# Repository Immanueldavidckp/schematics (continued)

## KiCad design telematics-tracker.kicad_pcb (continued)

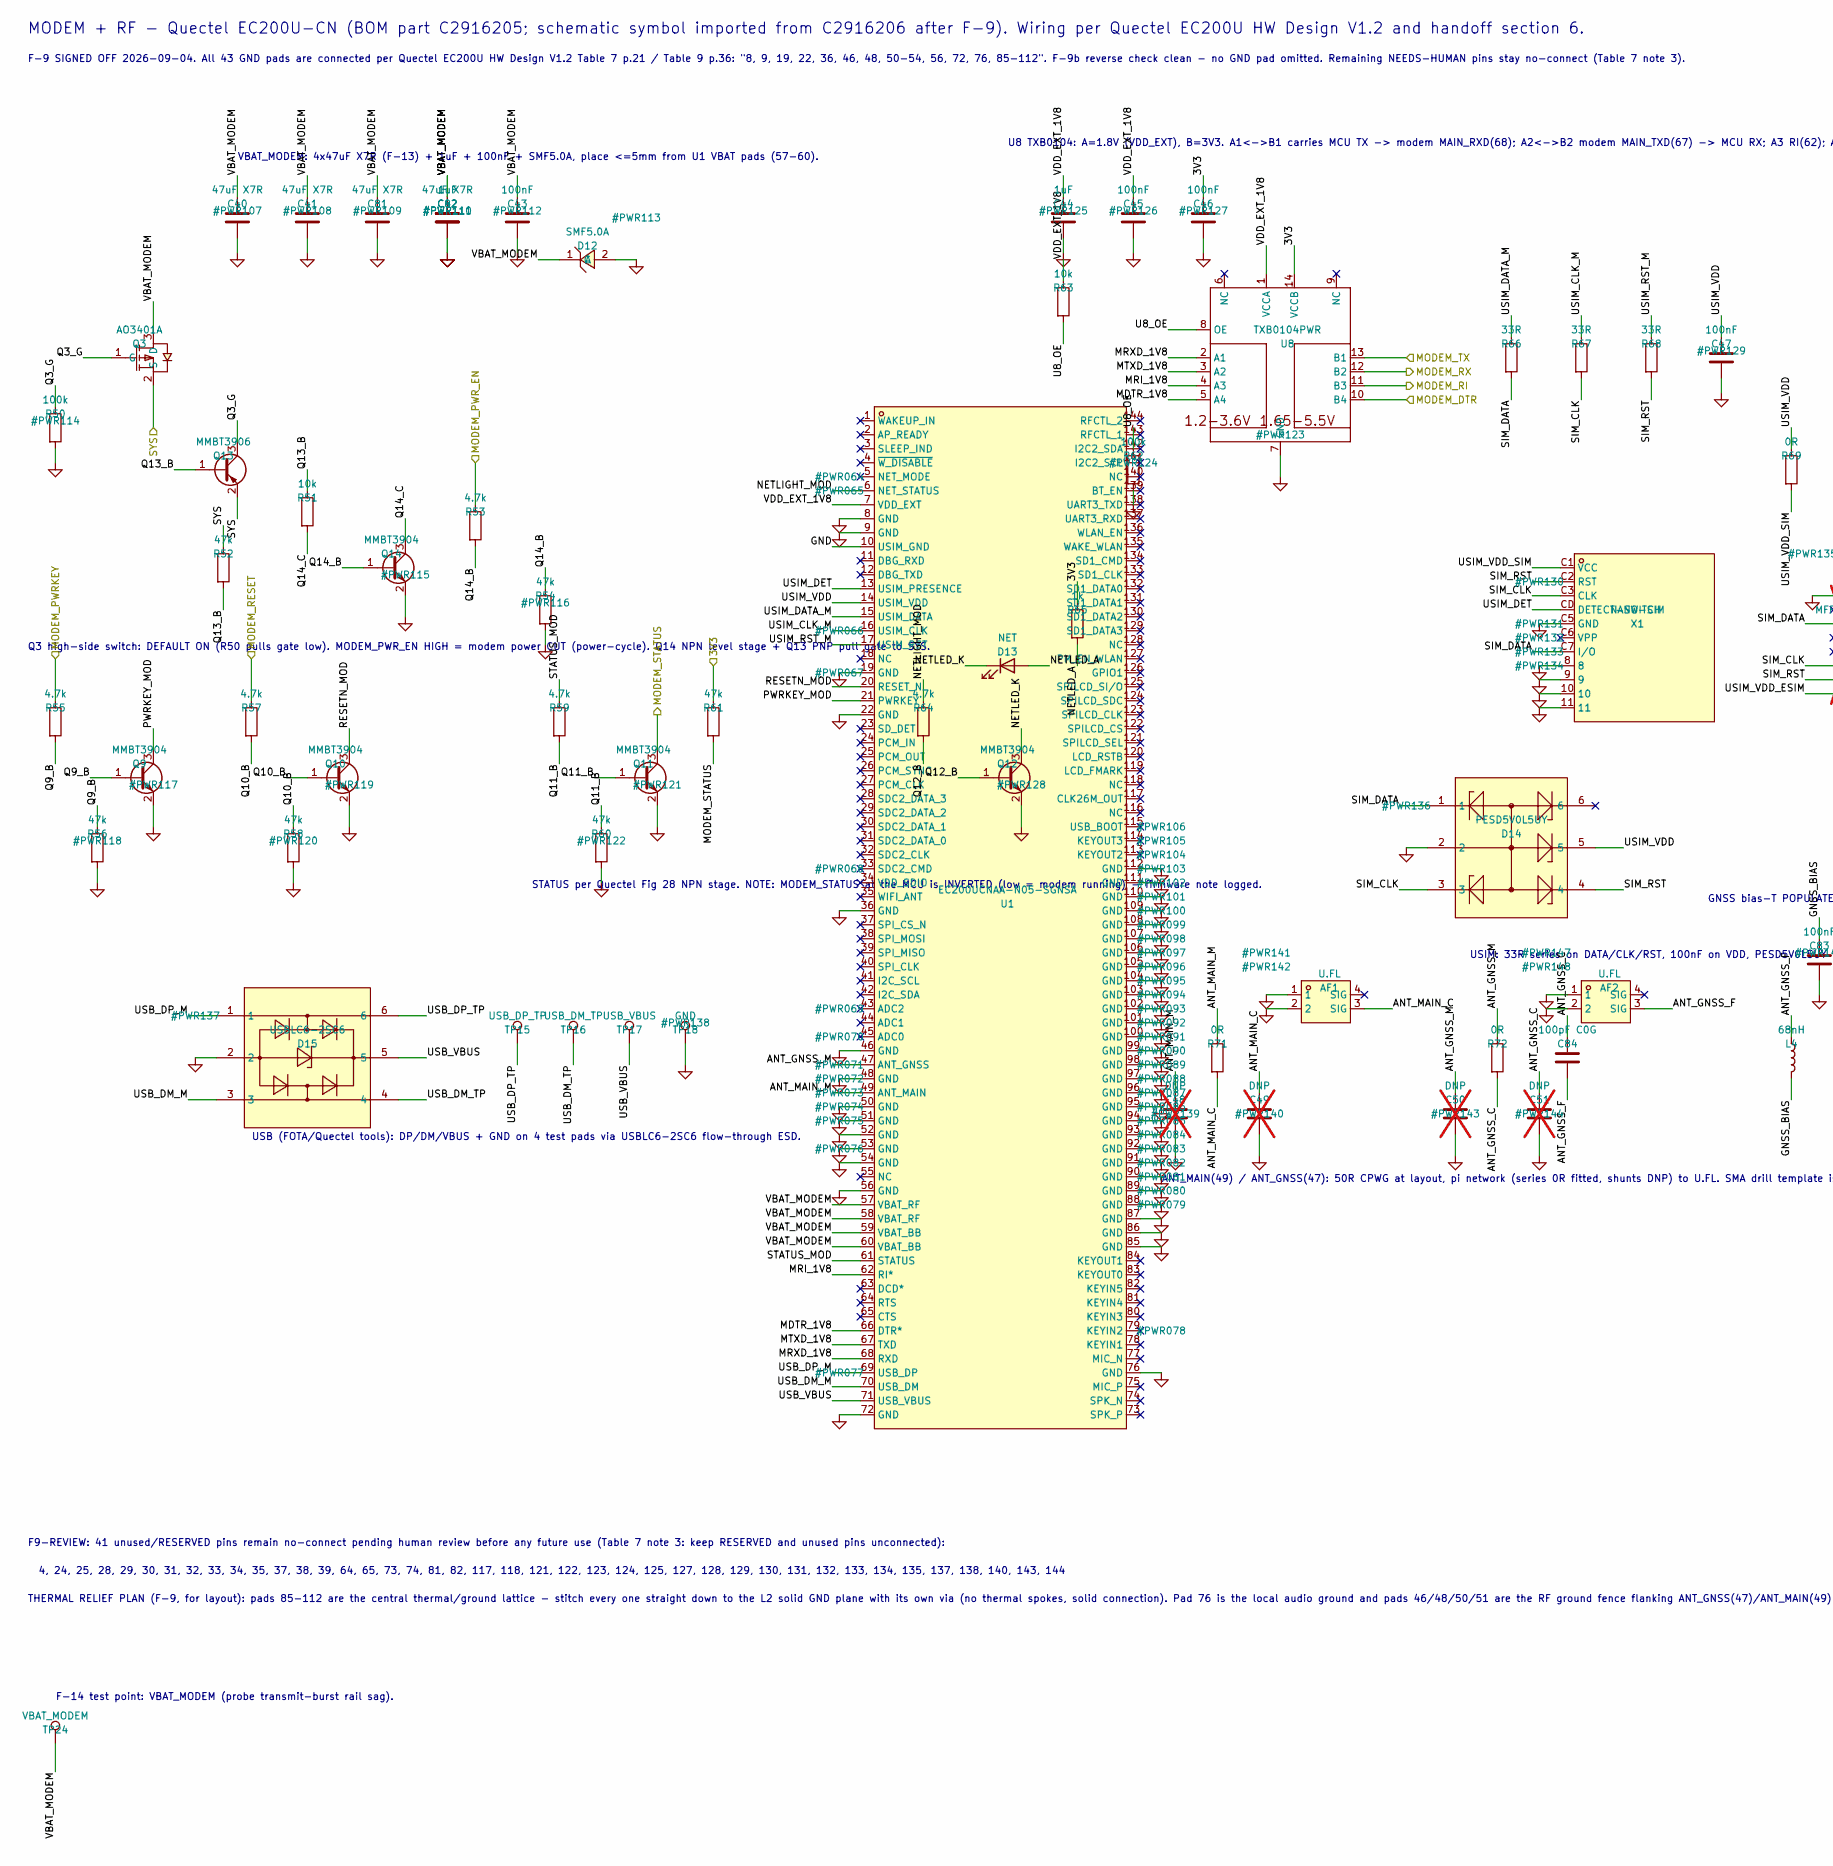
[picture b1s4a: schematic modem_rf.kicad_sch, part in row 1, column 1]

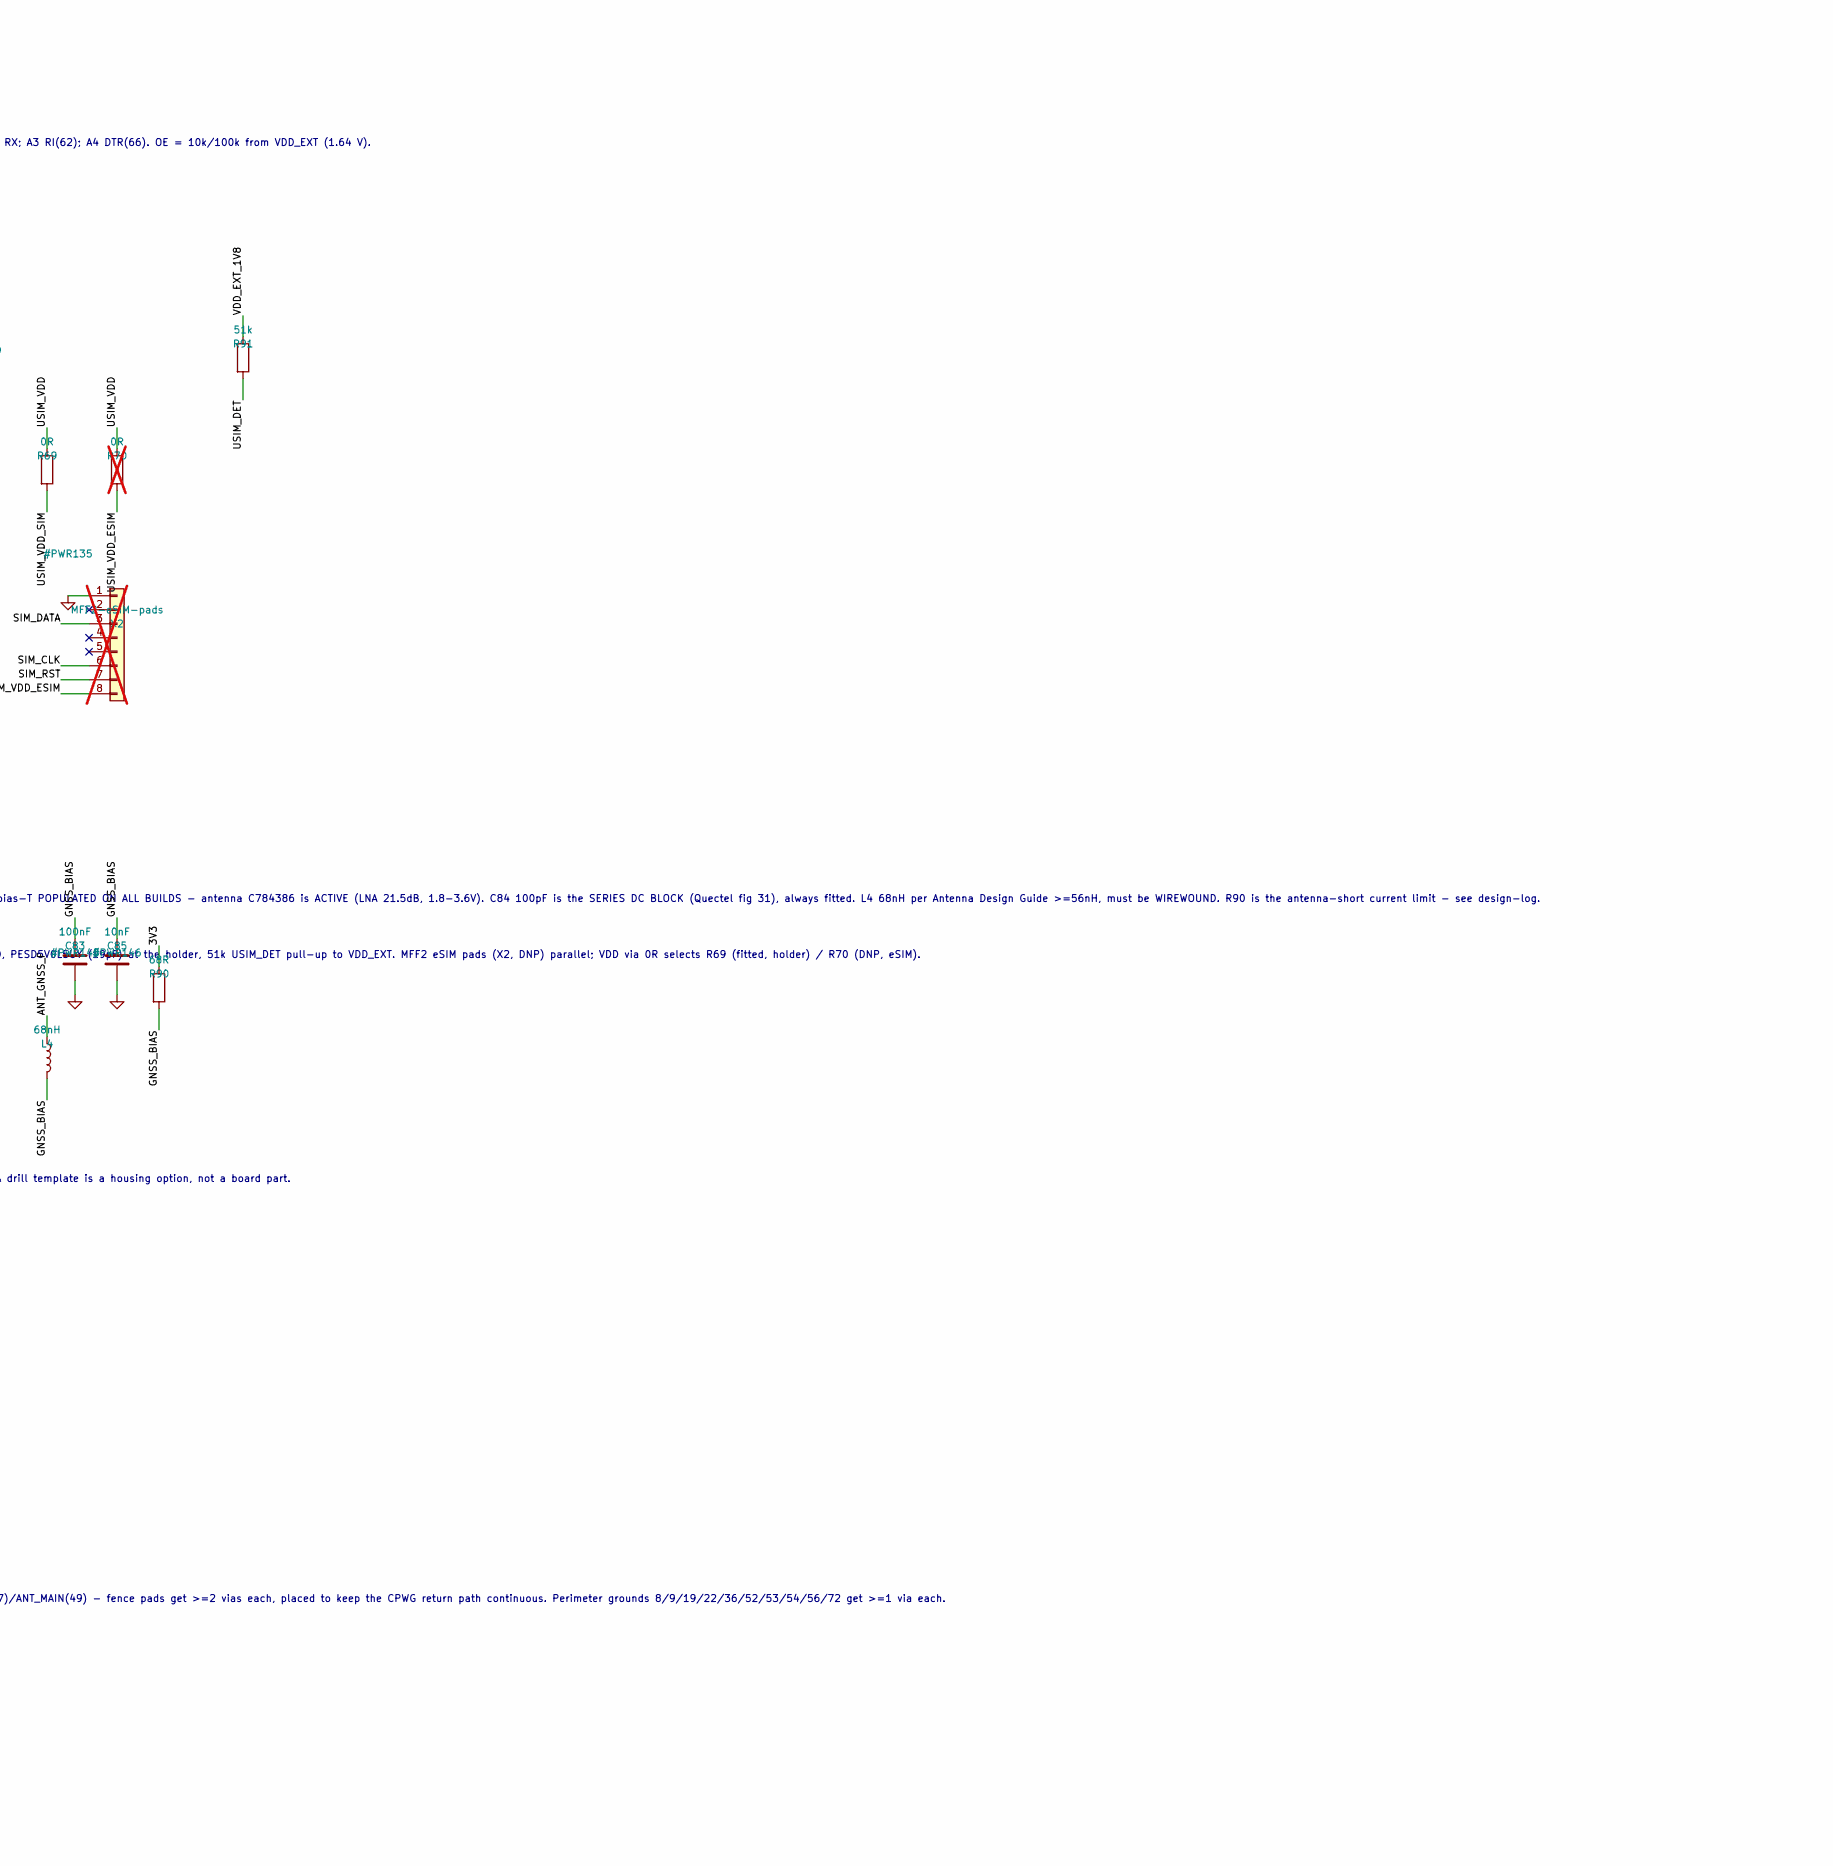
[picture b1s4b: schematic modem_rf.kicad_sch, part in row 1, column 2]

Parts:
AF1, AF2: U.FL; CONN-SMD_XY-IPEX1; LCSC C53133524
C40, C41, C81, C82: 47uF X7R; C_1210_3225Metric; LCSC C84494
C42, C44: 1uF; C_0603_1608Metric; LCSC C106858
C43, C45, C46, C47: 100nF; C_0603_1608Metric; LCSC C14663
C48, C49, C50, C51: DNP; C_0402_1005Metric; not fitted
C83: 100nF; C_0402_1005Metric; LCSC C1525
C84: 100pF C0G; C_0402_1005Metric; LCSC C1546
C85: 10nF; C_0402_1005Metric; LCSC C15195
D12: SMF5.0A; SOD-123FL_L2.7-W1.8-LS3.8-RD; LCSC C193402
D13: NET; LED_0603_1608Metric; LCSC C2286
D14: PESD5V0L5UY; SOT-363_L2.0-W1.3-P0.65-LS2.1-BR; LCSC C179747
D15: USBLC6-2SC6; SOT-23-6_L2.9-W1.6-P0.95-LS2.8-BL; LCSC C7519
L4: 68nH; L_0402_1005Metric; LCSC C3221844
Q3: AO3401A; SOT-23-3_L2.9-W1.3-P1.90-LS2.4-BR; LCSC C15127
Q9, Q10, Q11, Q12, Q14: MMBT3904; SOT-23; LCSC C20526
Q13: MMBT3906; SOT-23; LCSC C75549
R50, R62: 100k; R_0805_2012Metric; LCSC C149504
R51, R63: 10k; R_0805_2012Metric; LCSC C17414
R52, R54, R56, R58, R60, R61: 47k; R_0805_2012Metric; LCSC C17713
R53, R55, R57, R59, R64: 4.7k; R_0805_2012Metric; LCSC C17673
R65: 1k; R_0805_2012Metric; LCSC C17513
R66, R67, R68: 33R; R_0805_2012Metric; LCSC C17634
R69: 0R; R_0805_2012Metric; LCSC C17477
R70: 0R; R_0805_2012Metric; LCSC C17477; not fitted
R71, R72: 0R; R_0402_1005Metric; LCSC C17168
R90: 68R; R_1210_3225Metric; LCSC C137091
R91: 51k; R_0603_1608Metric; LCSC C23196
TP15: USB_DP_TP; TestPoint_Pad_D1.5mm
TP16: USB_DM_TP; TestPoint_Pad_D1.5mm
TP17: USB_VBUS; TestPoint_Pad_D1.5mm
TP18: GND; TestPoint_Pad_D1.5mm
TP24: VBAT_MODEM; TestPoint_Pad_D1.5mm
U1: EC200UCNAA-N05-SGNSA; LCC-LGA-144_L31.0-W28.0-P1.30_L610-CN-02; LCSC C2916205
U8: TXB0104PWR; TSSOP-14_L5.0-W4.4-P0.65-LS6.4-BL; LCSC C60708
X1: NANO-SIM; SIM-SMD_YKSIM-PUSH137-140NANO; LCSC C53207808
X2: MFF2-eSIM-pads; eSIM_MFF2_VFDFPN8; LCSC DNP-MFF2; not fitted

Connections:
3V3: C46.1, R61.1, R65.1, R90.1, U8.14 (VCCB); also elsewhere on the board
/modem_rf/ANT_GNSS_C: C51.1, C84.1, R72.2
/modem_rf/ANT_GNSS_F: AF2.3 (SIG), C84.2, L4.1
/modem_rf/ANT_GNSS_M: C50.1, R72.1, U1.47 (ANT_GNSS)
/modem_rf/ANT_MAIN_C: AF1.3 (SIG), C49.1, R71.2
/modem_rf/ANT_MAIN_M: C48.1, R71.1, U1.49 (ANT_MAIN)
/modem_rf/GNSS_BIAS: C83.1, C85.1, L4.2, R90.2
/modem_rf/MDTR_1V8: U1.66 (DTR*), U8.5 (A4)
/modem_rf/MRI_1V8: U1.62 (RI*), U8.4 (A3)
/modem_rf/MRXD_1V8: U1.68 (RXD), U8.2 (A1)
/modem_rf/MTXD_1V8: U1.67 (TXD), U8.3 (A2)
/modem_rf/NETLED_A: D13.2 (A), R65.2
/modem_rf/NETLED_K: D13.1 (K), Q12.3 (C)
/modem_rf/NETLIGHT_MOD: R64.1, U1.6 (NET_STATUS)
/modem_rf/PWRKEY_MOD: Q9.3 (C), U1.21 (PWRKEY)
/modem_rf/Q3_G: Q3.1 (G), Q13.3 (C), R50.1
/modem_rf/Q9_B: Q9.1 (B), R55.2, R56.1
/modem_rf/Q10_B: Q10.1 (B), R57.2, R58.1
/modem_rf/Q11_B: Q11.1 (B), R59.2, R60.1
/modem_rf/Q12_B: Q12.1 (B), R64.2
/modem_rf/Q13_B: Q13.1 (B), R51.1, R52.2
/modem_rf/Q14_B: Q14.1 (B), R53.2, R54.1
/modem_rf/Q14_C: Q14.3 (C), R51.2
/modem_rf/RESETN_MOD: Q10.3 (C), U1.20 (RESET_N)
/modem_rf/SIM_CLK: D14.3, R67.2, X1.C3 (CLK), X2.6
/modem_rf/SIM_DATA: D14.1, R66.2, X1.C7 (I/O), X2.3
/modem_rf/SIM_RST: D14.4, R68.2, X1.C2 (RST), X2.7
/modem_rf/STATUS_MOD: R59.1, U1.61 (STATUS)
/modem_rf/U8_OE: R62.1, R63.2, U8.8 (OE)
/modem_rf/USB_DM_M: D15.3, U1.70 (USB_DM)
/modem_rf/USB_DM_TP: D15.4, TP16.1
/modem_rf/USB_DP_M: D15.1, U1.69 (USB_DP)
/modem_rf/USB_DP_TP: D15.6, TP15.1
/modem_rf/USB_VBUS: D15.5, TP17.1, U1.71 (USB_VBUS)
/modem_rf/USIM_CLK_M: R67.1, U1.16 (USIM_CLK)
/modem_rf/USIM_DATA_M: R66.1, U1.15 (USIM_DATA)
/modem_rf/USIM_DET: R91.2, U1.13 (USIM_PRESENCE), X1.CD (DETECT-SWITCH)
/modem_rf/USIM_RST_M: R68.1, U1.17 (USIM_RST)
/modem_rf/USIM_VDD: C47.1, D14.5, R69.1, R70.1, U1.14 (USIM_VDD)
/modem_rf/USIM_VDD_ESIM: R70.2, X2.8
/modem_rf/USIM_VDD_SIM: R69.2, X1.C1 (VCC)
/modem_rf/VBAT_MODEM: C40.1, C41.1, C42.1, C43.1, C81.1, C82.1, D12.1 (C), Q3.3 (D), TP24.1, U1.57 (VBAT_RF), U1.58 (VBAT_RF), U1.59 (VBAT_BB), U1.60 (VBAT_BB)
/modem_rf/VDD_EXT_1V8: C44.1, C45.1, R63.1, R91.1, U1.7 (VDD_EXT), U8.1 (VCCA)
GND: AF1.1, AF1.2, AF2.1, AF2.2, C40.2, C41.2, C42.2, C43.2, C44.2, C45.2, C46.2, C47.2, C48.2, C49.2, C50.2, C51.2, C81.2, C82.2, C83.2, C85.2, D12.2 (A), D14.2, D15.2, Q9.2 (E), Q10.2 (E), Q11.2 (E), Q12.2 (E), Q14.2 (E), R50.2, R54.2, R56.2, R58.2, R60.2, R62.2, TP18.1, U1.8 (GND), U1.9 (GND), U1.10 (USIM_GND), U1.19 (GND), U1.22 (GND), U1.36 (GND), U1.46 (GND), U1.48 (GND), U1.50 (GND), U1.51 (GND), U1.52 (GND), U1.53 (GND), U1.54 (GND), U1.56 (GND), U1.72 (GND), U1.76 (GND), U1.85 (GND), U1.86 (GND), U1.87 (GND), U1.88 (GND), U1.89 (GND), U1.90 (GND), U1.91 (GND), U1.92 (GND), U1.93 (GND), U1.94 (GND), U1.95 (GND), U1.96 (GND), U1.97 (GND), U1.98 (GND), U1.99 (GND), U1.100 (GND), U1.101 (GND), U1.102 (GND), U1.103 (GND), U1.104 (GND), U1.105 (GND), U1.106 (GND), U1.107 (GND), U1.108 (GND), U1.109 (GND), U1.110 (GND), U1.111 (GND), U1.112 (GND), U8.7 (GND), X1.8, X1.9, X1.10, X1.11, X1.C5 (GND), X2.1; also elsewhere on the board
MODEM_DTR: U8.10 (B4); also elsewhere on the board
MODEM_PWRKEY: R55.1; also elsewhere on the board
MODEM_PWR_EN: R53.1; also elsewhere on the board
MODEM_RESET: R57.1; also elsewhere on the board
MODEM_RI: U8.11 (B3); also elsewhere on the board
MODEM_RX: U8.12 (B2); also elsewhere on the board
MODEM_STATUS: Q11.3 (C), R61.2; also elsewhere on the board
MODEM_TX: U8.13 (B1); also elsewhere on the board
SYS: Q3.2 (S), Q13.2 (E), R52.1; also elsewhere on the board

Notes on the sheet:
MODEM + RF - Quectel EC200U-CN (BOM part C2916205; schematic symbol imported from C2916206 after F-9). Wiring per Quectel EC200U HW Design V1.2 and handoff section 6.
F-9 SIGNED OFF 2026-09-04. All 43 GND pads are connected per Quectel EC200U HW Design V1.2 Table 7 p.21 / Table 9 p.36: "8, 9, 19, 22, 36, 46, 48, 50-54, 56, 72, 76, 85-112". F-9b reverse check clean - no GND pad omitted. Remaining NEEDS-HUMAN pins stay no-connect (Table 7 note 3).
F9-REVIEW: 41 unused/RESERVED pins remain no-connect pending human review before any future use (Table 7 note 3: keep RESERVED and unused pins unconnected):
4, 24, 25, 28, 29, 30, 31, 32, 33, 34, 35, 37, 38, 39, 64, 65, 73, 74, 81, 82, 117, 118, 121, 122, 123, 124, 125, 127, 128, 129, 130, 131, 132, 133, 134, 135, 137, 138, 140, 143, 144
THERMAL RELIEF PLAN (F-9, for layout): pads 85-112 are the central thermal/ground lattice - stitch every one straight down to the L2 solid GND plane with its own via (no thermal spokes, solid connection). Pad 76 is the local audio ground and pads 46/48/50/51 are the RF ground fence flanking ANT_GNS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
VBAT_MODEM: 4x47uF X7R (F-13) + 1uF + 100nF + SMF5.0A, place <=5mm from U1 VBAT pads (57-60).
F-14 test point: VBAT_MODEM (probe transmit-burst rail sag).
Q3 high-side switch: DEFAULT ON (R50 pulls gate low). MODEM_PWR_EN HIGH = modem power CUT (power-cycle). Q14 NPN level stage + Q13 PNP pull gate to SYS.
STATUS per Quectel Fig 28 NPN stage. NOTE: MODEM_STATUS at the MCU is INVERTED (low = modem running) - firmware note logged.
U8 TXB0104: A=1.8V (VDD_EXT), B=3V3. A1<->B1 carries MCU TX -> modem MAIN_RXD(68); A2<->B2 modem MAIN_TXD(67) -> MCU RX; A3 RI(62); A4 DTR(66). OE = 10k/100k from VDD_EXT (1.64 V).
USIM: 33R series on DATA/CLK/RST, 100nF on VDD, PESD5V0L5UY (19pF) at the holder, 51k USIM_DET pull-up to VDD_EXT. MFF2 eSIM pads (X2, DNP) parallel; VDD via 0R selects R69 (fitted, holder) / R70 (DNP, eSIM).
USB (FOTA/Quectel tools): DP/DM/VBUS + GND on 4 test pads via USBLC6-2SC6 flow-through ESD.
GNSS bias-T POPULATED ON ALL BUILDS - antenna C784386 is ACTIVE (LNA 21.5dB, 1.8-3.6V). C84 100pF is the SERIES DC BLOCK (Quectel fig 31), always fitted. L4 68nH per Antenna Design Guide >=56nH, must be WIREWOUND. R90 is the antenna-short current limit - see design-log.
ANT_MAIN(49) / ANT_GNSS(47): 50R CPWG at layout, pi network (series 0R fitted, shunts DNP) to U.FL. SMA drill template is a housing option, not a board part.

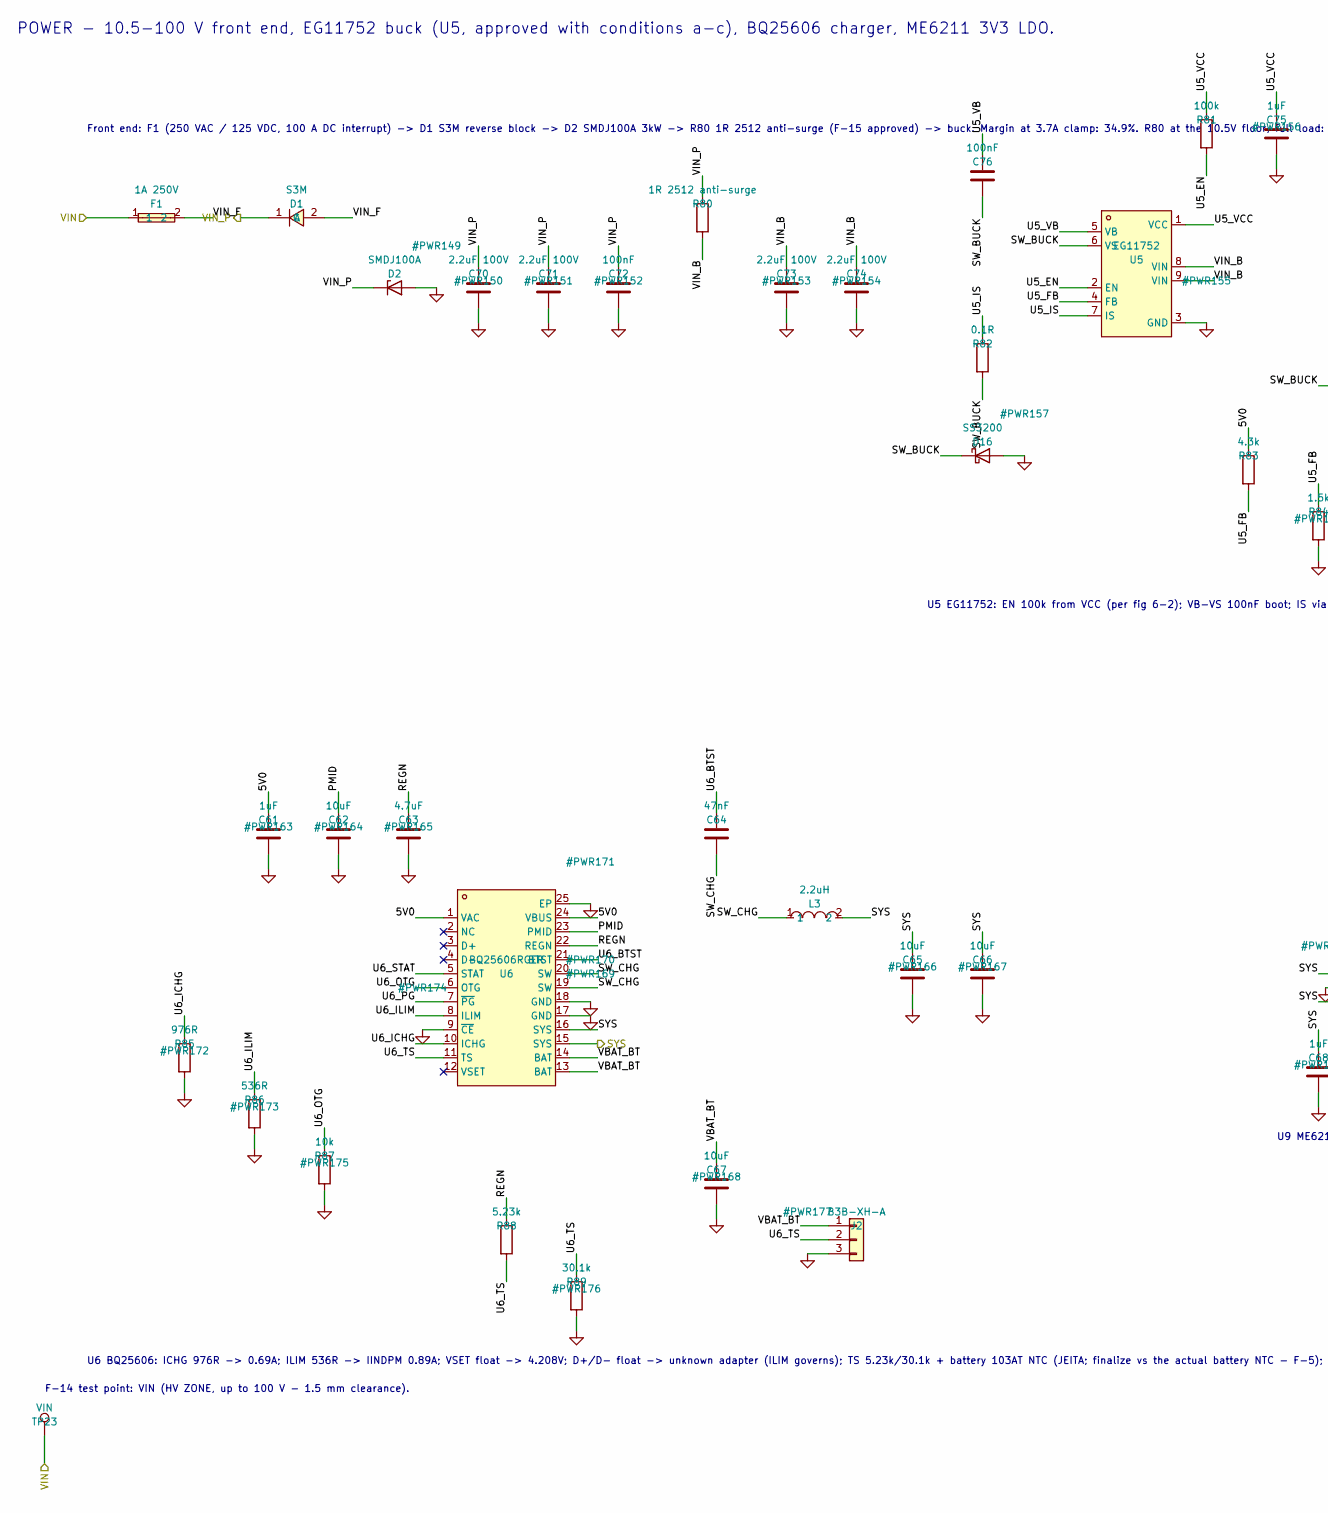
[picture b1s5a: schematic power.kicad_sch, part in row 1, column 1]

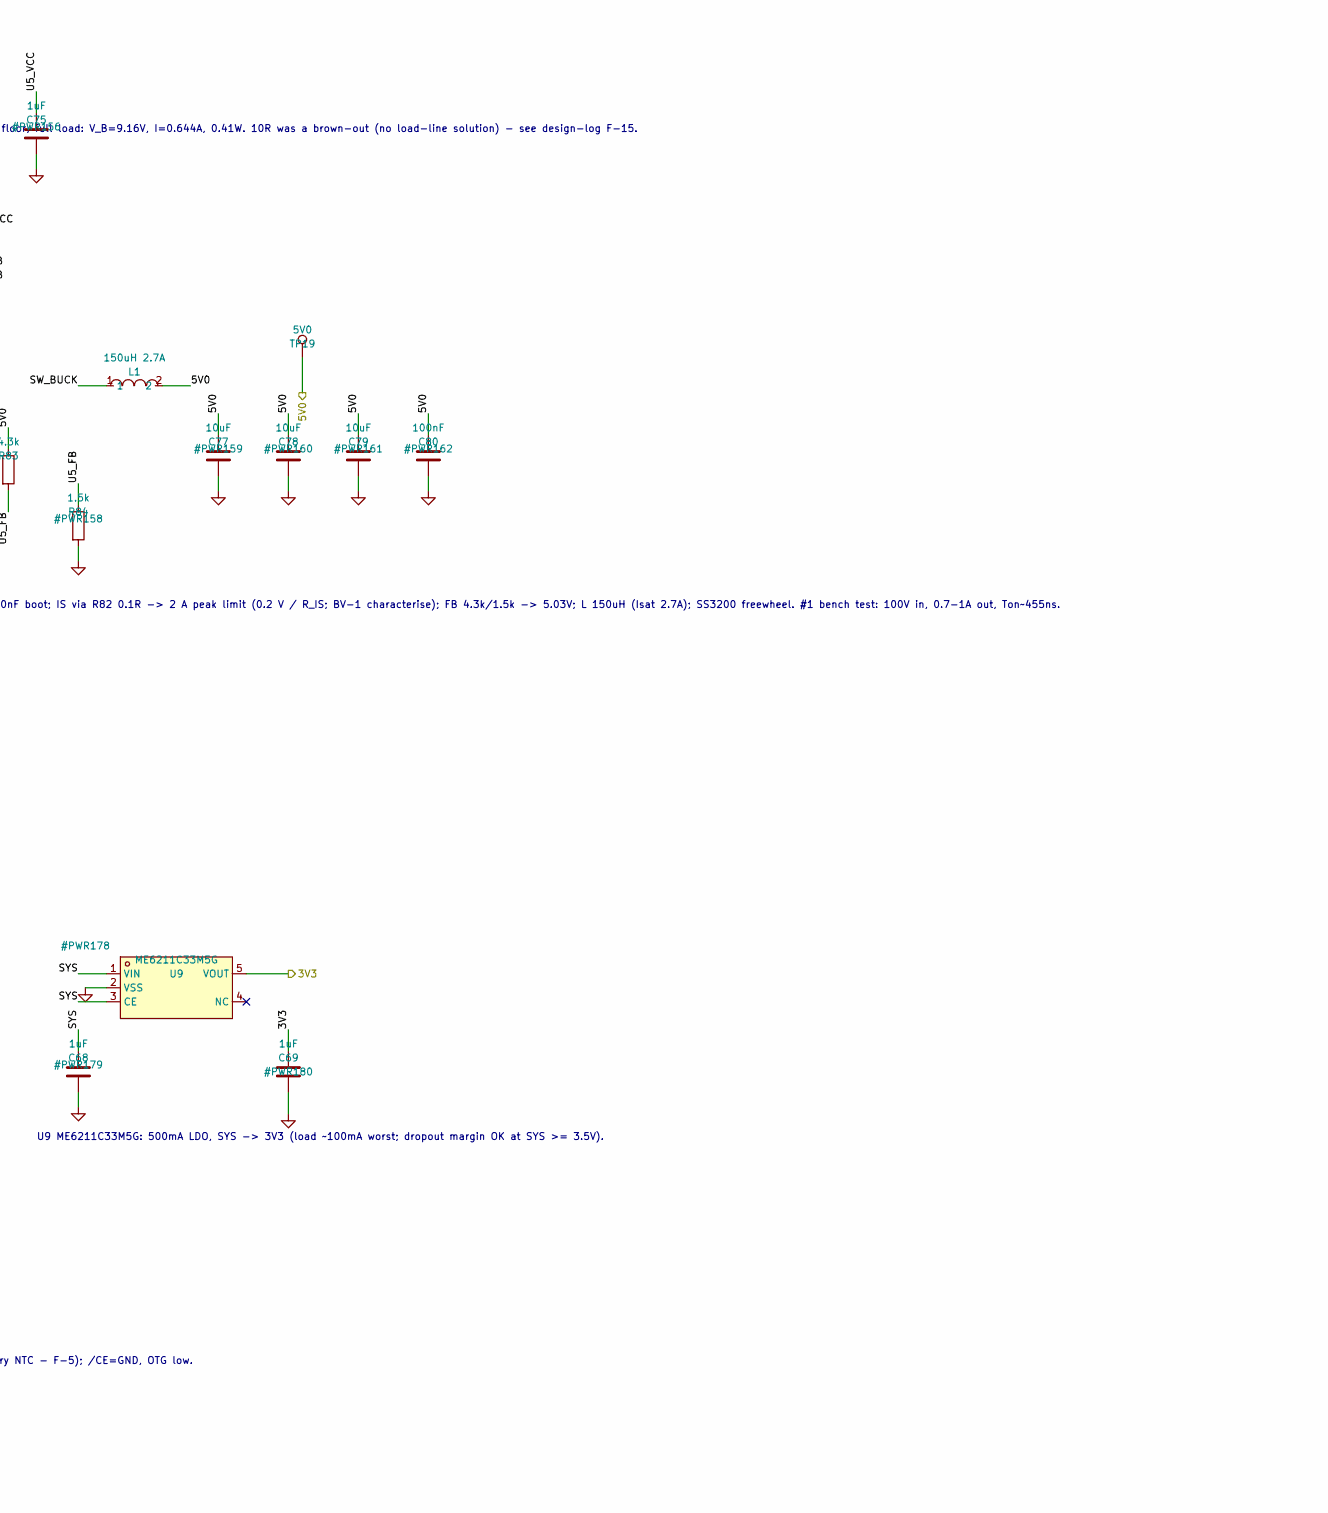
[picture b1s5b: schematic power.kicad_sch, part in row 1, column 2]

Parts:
C61, C68, C69, C75: 1uF; C_0603_1608Metric; LCSC C106858
C62, C65, C66, C67, C77, C78, C79: 10uF; C_0805_2012Metric; LCSC C109040
C63: 4.7uF; C_0805_2012Metric; LCSC C354262
C64: 47nF; C_0603_1608Metric; LCSC C1622
C70, C71, C73, C74: 2.2uF 100V; C_1210_3225Metric; LCSC C5449052
C72, C76, C80: 100nF; C_0603_1608Metric; LCSC C14663
D1: S3M; SMB_L4.3-W3.6-LS5.3-RD; LCSC C5204901
D2: SMDJ100A; D_SMC; LCSC C1977839
D16: SS3200; D_SMA; LCSC C65001
F1: 1A 250V; FUSE-SMD_L10.1-W3.1; LCSC C95352
J2: B3B-XH-A; JST_XH_B3B-XH-A_1x03_P2.50mm_Vertical; LCSC C144394
L1: 150uH 2.7A; IND-SMD_L12.3-W12.3; LCSC C21325
L3: 2.2uH; L1008; LCSC C391305
R80: 1R 2512 anti-surge; R_2512_6332Metric; LCSC C55348540
R81: 100k; R_0805_2012Metric; LCSC C149504
R82: 0.1R; R_0805_2012Metric; LCSC C327057
R83: 4.3k; R_0805_2012Metric; LCSC C17667
R84: 1.5k; R_0805_2012Metric; LCSC C4310
R85: 976R; R_0805_2012Metric; LCSC C17880
R86: 536R; R_0805_2012Metric; LCSC C5713309
R87: 10k; R_0805_2012Metric; LCSC C17414
R88: 5.23k; R_0805_2012Metric; LCSC C2933464
R89: 30.1k; R_0805_2012Metric; LCSC C21841
TP19: 5V0; TestPoint_Pad_D1.5mm
TP23: VIN; TestPoint_Pad_D1.5mm
U5: EG11752; SOIC-8_L4.9-W3.9-P1.27-LS6.0-BL-EP3.3-1; LCSC C53368402
U6: BQ25606RGER; VQFN-24_L4.0-W4.0-P0.50-TL-EP2.8; LCSC C374063
U9: ME6211C33M5G; SOT-23-5_L3.0-W1.7-P0.95-LS2.8-BL; LCSC C82942

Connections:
3V3: C69.1, U9.5 (VOUT); also elsewhere on the board
5V0: C61.1, C77.1, C78.1, C79.1, C80.1, L1.2, R83.1, TP19.1, U6.1 (VAC), U6.24 (VBUS); also elsewhere on the board
/power/PMID: C62.1, U6.23 (PMID)
/power/REGN: C63.1, R88.1, U6.22 (REGN)
/power/SW_BUCK: C76.2, D16.1 (K), L1.1, R82.2, U5.6 (VS)
/power/SW_CHG: C64.2, L3.1, U6.19 (SW), U6.20 (SW)
/power/U5_EN: R81.2, U5.2 (EN)
/power/U5_FB: R83.2, R84.1, U5.4 (FB)
/power/U5_IS: R82.1, U5.7 (IS)
/power/U5_VB: C76.1, U5.5 (VB)
/power/U5_VCC: C75.1, R81.1, U5.1 (VCC)
/power/U6_BTST: C64.1, U6.21 (BTST)
/power/U6_ICHG: R85.1, U6.10 (ICHG)
/power/U6_ILIM: R86.1, U6.8 (ILIM)
/power/U6_OTG: R87.1, U6.6 (OTG)
/power/U6_PG: U6.7 (~PG)
/power/U6_STAT: U6.5 (STAT)
/power/U6_TS: J2.2, R88.2, R89.1, U6.11 (TS)
/power/VBAT_BT: C67.1, J2.1, U6.13 (BAT), U6.14 (BAT)
/power/VIN_B: C73.1, C74.1, R80.2, U5.8 (VIN), U5.9 (VIN)
/power/VIN_F: D1.2 (A), F1.2
GND: C61.2, C62.2, C63.2, C65.2, C66.2, C67.2, C68.2, C69.2, C70.2, C71.2, C72.2, C73.2, C74.2, C75.2, C77.2, C78.2, C79.2, C80.2, D2.2 (A), D16.2 (A), J2.3, R84.2, R85.2, R86.2, R87.2, R89.2, U5.3 (GND), U6.9 (~CE), U6.17 (GND), U6.18 (GND), U6.25 (EP), U9.2 (VSS); also elsewhere on the board
SYS: C65.1, C66.1, C68.1, L3.2, U6.15 (SYS), U6.16 (SYS), U9.1 (VIN), U9.3 (CE); also elsewhere on the board
VIN: F1.1, TP23.1; also elsewhere on the board
VIN_P: C70.1, C71.1, C72.1, D1.1 (C), D2.1 (K), R80.1; also elsewhere on the board

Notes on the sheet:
POWER - 10.5-100 V front end, EG11752 buck (U5, approved with conditions a-c), BQ25606 charger, ME6211 3V3 LDO.
Front end: F1 (250 VAC / 125 VDC, 100 A DC interrupt) -> D1 S3M reverse block -> D2 SMDJ100A 3kW -> R80 1R 2512 anti-surge (F-15 approved) -> buck. Margin at 3.7A clamp: 34.9%. R80 at the 10.5V floor, full load: V_B=9.16V, I=0.644A, 0.41W. 10R was a brown-out (no load-line solution) - see design-lo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
F-14 test point: VIN (HV ZONE, up to 100 V - 1.5 mm clearance).
U5 EG11752: EN 100k from VCC (per fig 6-2); VB-VS 100nF boot; IS via R82 0.1R -> 2 A peak limit (0.2 V / R_IS; BV-1 characterise); FB 4.3k/1.5k -> 5.03V; L 150uH (Isat 2.7A); SS3200 freewheel. #1 bench test: 100V in, 0.7-1A out, Ton~455ns.
U6 BQ25606: ICHG 976R -> 0.69A; ILIM 536R -> IINDPM 0.89A; VSET float -> 4.208V; D+/D- float -> unknown adapter (ILIM governs); TS 5.23k/30.1k + battery 103AT NTC (JEITA; finalize vs the actual battery NTC - F-5); /CE=GND, OTG low.
U9 ME6211C33M5G: 500mA LDO, SYS -> 3V3 (load ~100mA worst; dropout margin OK at SYS >= 3.5V).
